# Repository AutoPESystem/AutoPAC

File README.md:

# AutoPAC
This repository will contain the relevant firmware and hardware for an automated PAC (Pump Assisted Clamping) Device.

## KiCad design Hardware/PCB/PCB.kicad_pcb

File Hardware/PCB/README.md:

# PCB
This is a KiCAD PCB project that contains the hardware implementation required for the AutoPAC device.

This includes a vacuum sensor, positive pressure sensor, circuitry to drive 2 brushed motors, circuitry to control multiple solenoid relays, and an LCD interface over SPI.

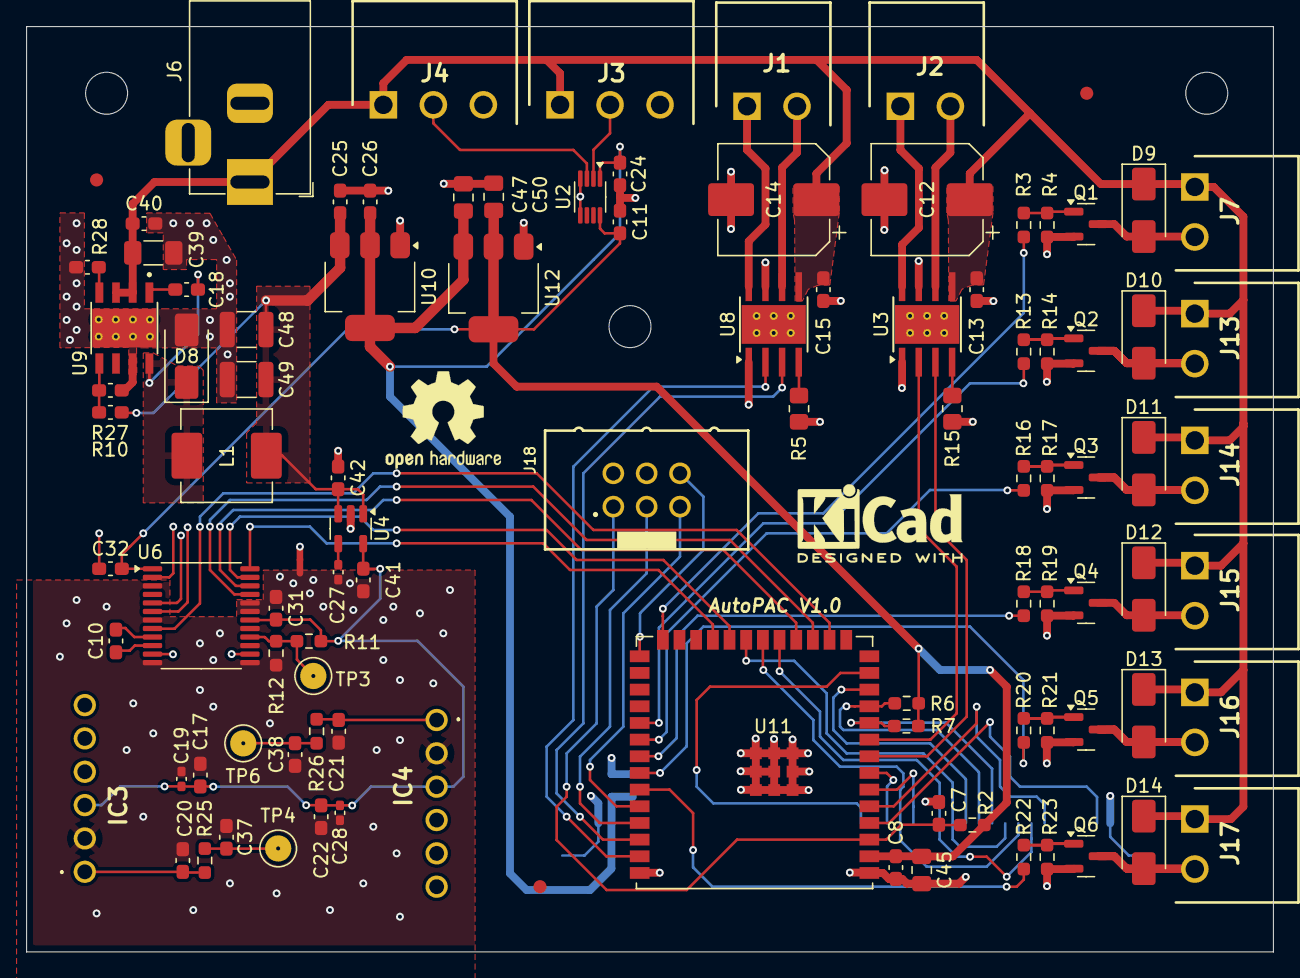
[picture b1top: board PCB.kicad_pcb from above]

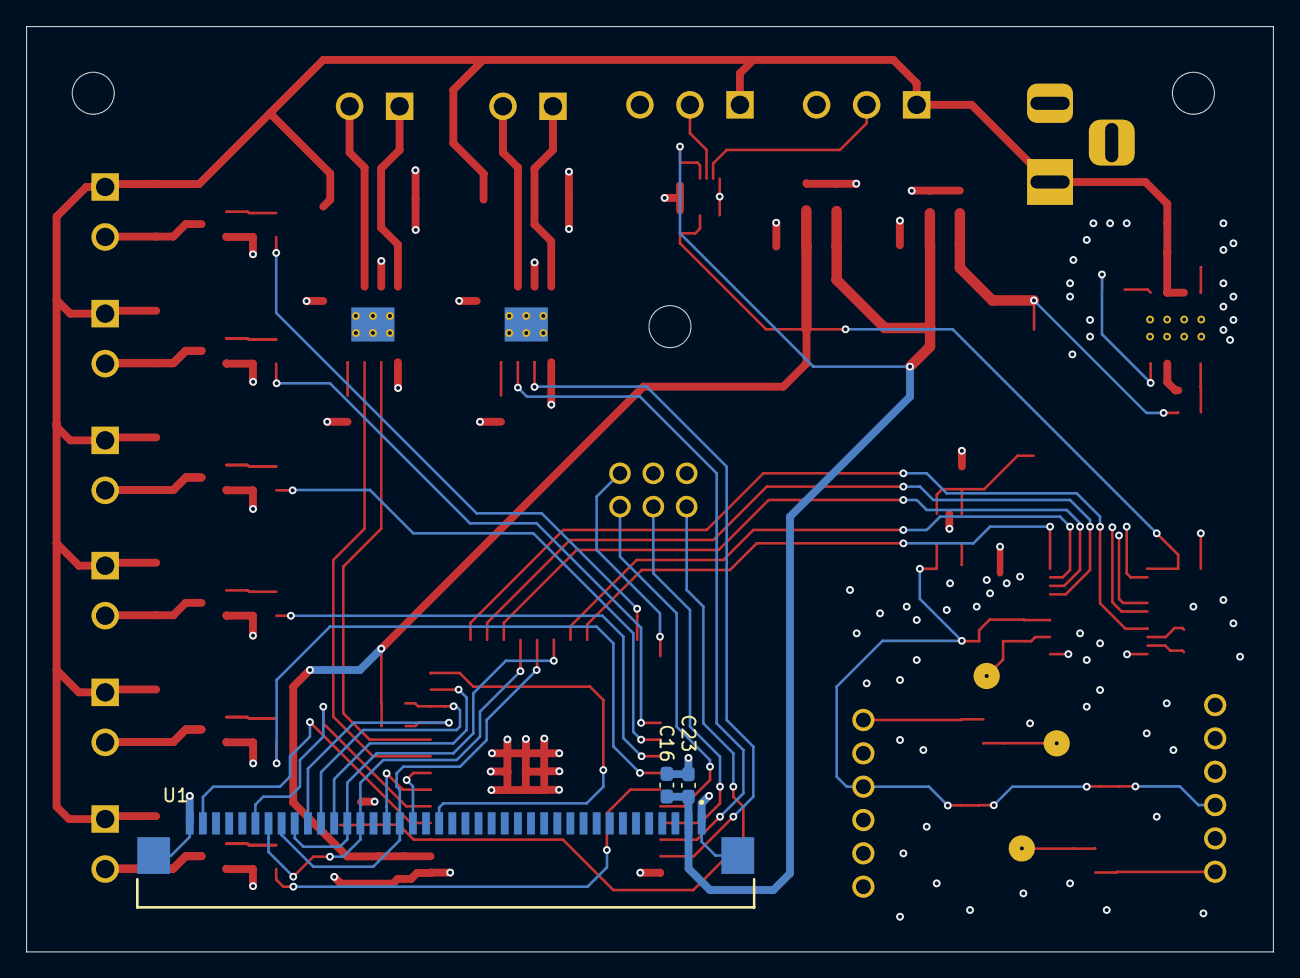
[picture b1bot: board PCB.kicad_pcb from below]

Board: 4 copper layers, 95.0 x 70.5 mm, 103 parts (3 on the bottom side), 69 nets.

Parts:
C7, C17, C22, C41, C42: 1uF; C_0603_1608Metric_Pad1.08x0.95mm_HandSolder
C8, C10, C11, C13, C15, C18, C23, C24, C31, C32, C40: 100nF; C_0603_1608Metric_Pad1.08x0.95mm_HandSolder
C12, C14: 22uF; CP_Elec_8x10
C16, C25, C26: 10uF; C_0603_1608Metric_Pad1.08x0.95mm_HandSolder
C19, C27, C28: 0.01uF; C_0402_1005Metric_Pad0.74x0.62mm_HandSolder
C20, C21: 470pF; C_0603_1608Metric_Pad1.08x0.95mm_HandSolder
C37, C38: 0.33uF; C_0603_1608Metric_Pad1.08x0.95mm_HandSolder
C39: 10uF; C_1206_3216Metric_Pad1.33x1.80mm_HandSolder
C45, C47, C50: 22uF; C_0805_2012Metric_Pad1.18x1.45mm_HandSolder
C48, C49: 47uF; C_1210_3225Metric
D8, D9, D10, D11, D12, D13, D14: SS310; D_SMA
H1, H2, H4: MountingHole; MountingHole_3.2mm_M3
IC3, IC4: MPX5500DP
J1, J2: Pump Motor; CONN_WJ15EDGRC-3.81-2P
J3, J4: BLDC Motor; CONN_WJ15EDGRC-3.81-3P
J6: XUNPU DC-005-A250; BarrelJack_Horizontal
J7, J13, J14, J15, J16, J17: Solenoid Terminal; CONN_WJ15EDGRC-3.81-2P
J18: Programmer; 61200621621
L1: 6.8uH; L_Changjiang_FXL0630
NT1: NetTie_2; NetTie-2_SMD_Pad0.5mm
Q1, Q2, Q3, Q4, Q5, Q6: MMBT2222A; SOT-23
R2, R4, R14, R17, R19, R21, R23: 10k; R_0603_1608Metric_Pad0.98x0.95mm_HandSolder
R3, R13, R16, R18, R20, R22: 470; R_0603_1608Metric_Pad0.98x0.95mm_HandSolder
R5, R15: 18k; R_0805_2012Metric_Pad1.20x1.40mm_HandSolder
R6, R7: 2.2k; R_0603_1608Metric_Pad0.98x0.95mm_HandSolder
R10: 66.5k; C_0603_1608Metric_Pad1.08x0.95mm_HandSolder
R11: 300; R_0603_1608Metric_Pad0.98x0.95mm_HandSolder
R12: 4.7k; R_0603_1608Metric_Pad0.98x0.95mm_HandSolder
R25, R26: 750; R_0603_1608Metric_Pad0.98x0.95mm_HandSolder
R27: 10.5k; C_0603_1608Metric_Pad1.08x0.95mm_HandSolder
R28: 45.3k; C_0603_1608Metric_Pad1.08x0.95mm_HandSolder
TP3, TP4, TP6: TestPoint_Probe; TestPoint_Keystone_5000-5004_Miniature
U1: ER-TFTM032-3; GCT_FFC3B07-40-T
U2: SN74LVC2T45DCUR; VSSOP-8_2.3x2mm_P0.5mm
U3, U8: DRV8871DDA; Texas_HTSOP-8-1EP_3.9x4.9mm_P1.27mm_EP2.95x4.9mm_Mask2.4x3.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
U4: SPX5205M5-L-5-0/TR; SOT-23-5
U6: ADS1232IPW; TSSOP-24_6.1x7.8mm_P0.65mm
U9: LMR16030PDDAR; VREG_LM5017MR_NOPB
U10: AZ1117-5.0; SOT-223-3_TabPin2
U11: ESP32-S3-WROOM-1U-N16R8; XCVR_ESP32-S3-WROOM-1U-N16R8
U12: AZ1117-3.3; SOT-223-3_TabPin2

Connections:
+3.3V: C8.2, C11.1, C32.1, C45.2, C50.1, R2.1, R6.1, R7.1, U2.8 (VCCB), U6.1 (DVDD), U11.2 (3V3), U12.2 (VO)
+4.7V: R11.2, R12.1, TP3.1, U6.16 (REFP)
+5.5V: C25.1, C42.2, C48.1, C49.1, L1.2, R10.1, U4.1 (IN), U4.3 (EN), U10.3 (VI)
+5V: C16.2, C23.2, C24.1, C26.1, C47.1, U1.2 (VDD), U2.1 (VCCA), U10.2 (VO), U12.3 (VI)
+5VA: C17.1, C19.1, C22.1, C28.1, C31.1, C41.2, IC3.3 (VCC), IC4.3 (VCC), R11.1, U4.5 (OUT), U6.18 (AVDD)
+24V: C12.1, C13.1, C14.1, C15.1, C39.1, C40.2, D9.1 (K), D10.1 (K), D11.1 (K), D12.1 (K), D13.1 (K), D14.1 (K), J3.1, J4.1, J6.1, J7.1, J13.1, J14.1, J15.1, J16.1, J17.1, U3.5 (VM), U8.5 (VM), U9.2 (VIN), U9.3 (EN)
/CTP-INT: U1.39 (CTP_INT), U11.4 (IO4)
/DISP-BACKLIGHT: U1.29 (BL_ON/OFF), U11.12 (IO8)
/DISP-CS: U1.23 (LCD_CS), U11.7 (IO7)
/DISP-DC: U1.25 (/WR(D/C)), U11.6 (IO6)
/DISP-RESET: U1.21 (RESET), U11.13 (IO19)
/ESP32-S3/BOOT: J18.6, U11.27 (IO0)
/ESP32-S3/EN: C7.2, J18.1, R2.2, U11.3 (EN)
/ESP32-S3/RX: J18.5, U11.36 (RXD0)
/ESP32-S3/TX: J18.3, U11.37 (TXD0)
/GPIO9: U6.21 (SPEED), U11.17 (IO9)
/GPIO10: U6.22 (~PWDN), U11.18 (IO10)
/GPIO14: U6.23 (SCLK), U11.22 (IO14)
/GPIO21: U6.24 (~DRDY/DOUT), U11.23 (IO21)
/GPIO46: U6.8 (A0), U11.16 (IO46)
/I2C-SCL: R6.2, U1.30 (CTP_SCL), U11.11 (IO18)
/I2C-SDA: R7.2, U1.31 (CTP_SDA), U11.10 (IO17)
/PUMP-IN1: U3.3 (IN1), U11.8 (IO15)
/PUMP-IN2: U3.2 (IN2), U11.9 (IO16)
/SOLENOID_1: R3.1, U11.26 (IO45)
/SOLENOID_2: R13.1, U11.31 (IO38)
/SOLENOID_3: R16.1, U11.32 (IO39)
/SOLENOID_4: R18.1, U11.33 (IO40)
/SOLENOID_5: R20.1, U11.34 (IO41)
/SOLENOID_6: R22.1, U11.35 (IO42)
/SPI-CLK: U1.24 (D/C(SCL)), U1.33 (SCLK), U11.20 (IO12)
/SPI-MISO: U1.28 (LCD_SDO), U1.32 (SDO), U11.21 (IO13)
/SPI-MOSI: U1.27 (LCD_SDI), U1.34 (SDI), U11.19 (IO11)
/VAC-IN1: U8.3 (IN1), U11.38 (IO2)
/VAC-IN2: U8.2 (IN2), U11.39 (IO1)
/buck/FB: R10.2, R27.1, U9.5 (FB)
/sensors/pressure_sensor1/SENSOR_VOUT: C38.2, R26.2, TP6.1, U6.14 (AINP2)
/sensors/pressure_sensor/SENSOR_VOUT: C37.2, R25.2, TP4.1, U6.11 (AINP1)
/uSD-CS: U1.35 (SD_/CS), U11.5 (IO5)
GND: C7.1, C8.1, C11.2, C12.2, C13.2, C14.2, C15.2, C16.1, C23.1, C24.2, C25.2, C26.2, C32.2, C39.2, C40.1, C42.1, C45.1, C47.2, C48.2, C49.2, C50.2, D8.2 (A), J3.3, J4.3, J6.2, J18.4, NT1.2, Q1.2 (E), Q2.2 (E), Q3.2 (E), Q4.2 (E), Q5.2 (E), Q6.2 (E), R4.2, R5.2, R14.2, R15.2, R17.2, R19.2, R21.2, R23.2, R27.2, R28.2, U1.1 (GND), U1.40 (GND), U1.S1, U1.S2, U2.4 (GND), U2.5 (DIR), U3.1 (GND), U3.7 (GND), U3.9 (GND), U4.2 (GND), U6.2 (DGND), U6.5 (DGND), U6.6 (DGND), U8.1 (GND), U8.7 (GND), U8.9 (GND), U9.7 (GND), U9.9 (THERMALPAD), U9.10, U9.11, U9.12, U9.13, U9.14, U9.15, U9.16, U9.17, U10.1 (GND), U11.1 (GND), U11.40 (GND__1), U11.41_1 (GND__2), U11.41_2 (GND__3), U11.41_3 (GND__4), U11.41_4 (GND__5), U11.41_5 (GND__6), U11.41_6 (GND__7), U11.41_7 (GND__8), U11.41_8 (GND__9), U11.41_9 (GND__10), U12.1 (GND)
GNDA: C17.2, C19.2, C20.1, C21.1, C22.2, C27.1, C28.2, C31.2, C37.1, C38.1, C41.1, IC3.2 (GROUND), IC4.2 (GROUND), NT1.1, R12.2, U6.3 (CLKIN/XTAL1), U6.7 (TEMP), U6.12 (AINN1), U6.13 (AINN2), U6.15 (REFN), U6.17 (AGND), U6.19 (GAIN0), U6.20 (GAIN1)
unnamed: C10.1, U6.9 (CAP)
unnamed: C10.2, U6.10 (CAP)
unnamed: C18.2, D8.1 (K), L1.1, U9.8 (SW)
unnamed: D9.2 (A), J7.2, Q1.3 (C)
unnamed: D10.2 (A), J13.2, Q2.3 (C)
unnamed: D11.2 (A), J14.2, Q3.3 (C)
unnamed: D12.2 (A), J15.2, Q4.3 (C)
unnamed: D13.2 (A), J16.2, Q5.3 (C)
unnamed: D14.2 (A), J17.2, Q6.3 (C)
unnamed: C20.2, IC3.1 (VOUT), R25.1
unnamed: C21.2, IC4.1 (VOUT), R26.1
unnamed: J1.1, U8.8 (OUT2)
unnamed: J1.2, U8.6 (OUT1)
unnamed: J2.1, U3.8 (OUT2)
unnamed: J2.2, U3.6 (OUT1)
unnamed: J3.2, U2.2 (A1)
unnamed: J4.2, U2.3 (A2)
unnamed: Q1.1 (B), R3.2, R4.1
unnamed: Q2.1 (B), R13.2, R14.1
unnamed: Q3.1 (B), R16.2, R17.1
unnamed: Q4.1 (B), R18.2, R19.1
unnamed: Q5.1 (B), R20.2, R21.1
unnamed: Q6.1 (B), R22.2, R23.1
unnamed: R15.1, U3.4 (ILIM)
unnamed: C27.2, U4.4 (BP)
unnamed: R5.1, U8.4 (ILIM)
unnamed: C18.1, U9.1 (BOOT)
unnamed: R28.1, U9.4 (RT/SYNC)

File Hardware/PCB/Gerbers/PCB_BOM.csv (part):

Comment,Designator,Footprint,LCSC Part Number
50V 1uF X5R ±10% 0603 Multilayer Ceramic Capacitors MLCC - SMD/SMT ROHS,C7,Capacitor_SMD:C_0603_1608Metric_Pad1.08x0.95mm_HandSolder,C15849
50V 100nF X7R ±10% 0603 Multilayer Ceramic Capacitors MLCC - SMD/SMT ROHS,C8,Capacitor_SMD:C_0603_1608Metric_Pad1.08x0.95mm_HandSolder,C14663
50V 100nF X7R ±10% 0603 Multilayer Ceramic Capacitors MLCC - SMD/SMT ROHS,C10,Capacitor_SMD:C_0603_1608Metric_Pad1.08x0.95mm_HandSolder,C14663
50V 100nF X7R ±10% 0603 Multilayer Ceramic Capacitors MLCC - SMD/SMT ROHS,C11,Capacitor_SMD:C_0603_1608Metric_Pad1.08x0.95mm_HandSolder,C14663
"22uF 100V ±20% SMD,D8xL10.5mm Aluminum Electrolytic Capacitors - SMD ROHS",C12,Capacitor_SMD:CP_Elec_8x10,C29144
50V 100nF X7R ±10% 0603 Multilayer Ceramic Capacitors MLCC - SMD/SMT ROHS,C13,Capacitor_SMD:C_0603_1608Metric_Pad1.08x0.95mm_HandSolder,C14663
"22uF 100V ±20% SMD,D8xL10.5mm Aluminum Electrolytic Capacitors - SMD ROHS",C14,Capacitor_SMD:CP_Elec_8x10,C29144
50V 100nF X7R ±10% 0603 Multilayer Ceramic Capacitors MLCC - SMD/SMT ROHS,C15,Capacitor_SMD:C_0603_1608Metric_Pad1.08x0.95mm_HandSolder,C14663
25V 10uF X5R ±20% 0603 Multilayer Ceramic Capacitors MLCC - SMD/SMT ROHS,C16,Capacitor_SMD:C_0603_1608Metric_Pad1.08x0.95mm_HandSolder,C96446
50V 1uF X5R ±10% 0603 Multilayer Ceramic Capacitors MLCC - SMD/SMT ROHS,C17,Capacitor_SMD:C_0603_1608Metric_Pad1.08x0.95mm_HandSolder,C15849
50V 100nF X7R ±10% 0603 Multilayer Ceramic Capacitors MLCC - SMD/SMT ROHS,C18,Capacitor_SMD:C_0603_1608Metric_Pad1.08x0.95mm_HandSolder,C14663
10000 pF ±10% 50V Ceramic Capacitor X7R 0402 (1005 Metric),C19,Capacitor_SMD:C_0402_1005Metric_Pad0.74x0.62mm_HandSolder,C15195
50V 470pF NP0 ±5% 0603 Multilayer Ceramic Capacitors MLCC - SMD/SMT ROHS,C20,Capacitor_SMD:C_0603_1608Metric_Pad1.08x0.95mm_HandSolder,C106211
50V 470pF NP0 ±5% 0603 Multilayer Ceramic Capacitors MLCC - SMD/SMT ROHS,C21,Capacitor_SMD:C_0603_1608Metric_Pad1.08x0.95mm_HandSolder,C106211
50V 1uF X5R ±10% 0603 Multilayer Ceramic Capacitors MLCC - SMD/SMT ROHS,C22,Capacitor_SMD:C_0603_1608Metric_Pad1.08x0.95mm_HandSolder,C15849
50V 100nF X7R ±10% 0603 Multilayer Ceramic Capacitors MLCC - SMD/SMT ROHS,C23,Capacitor_SMD:C_0603_1608Metric_Pad1.08x0.95mm_HandSolder,C14663
50V 100nF X7R ±10% 0603 Multilayer Ceramic Capacitors MLCC - SMD/SMT ROHS,C24,Capacitor_SMD:C_0603_1608Metric_Pad1.08x0.95mm_HandSolder,C14663
25V 10uF X5R ±20% 0603 Multilayer Ceramic Capacitors MLCC - SMD/SMT ROHS,C25,Capacitor_SMD:C_0603_1608Metric_Pad1.08x0.95mm_HandSolder,C96446
25V 10uF X5R ±20% 0603 Multilayer Ceramic Capacitors MLCC - SMD/SMT ROHS,C26,Capacitor_SMD:C_0603_1608Metric_Pad1.08x0.95mm_HandSolder,C96446
10000 pF ±10% 50V Ceramic Capacitor X7R 0402 (1005 Metric),C27,Capacitor_SMD:C_0402_1005Metric_Pad0.74x0.62mm_HandSolder,C15195
10000 pF ±10% 50V Ceramic Capacitor X7R 0402 (1005 Metric),C28,Capacitor_SMD:C_0402_1005Metric_Pad0.74x0.62mm_HandSolder,C15195
50V 100nF X7R ±10% 0603 Multilayer Ceramic Capacitors MLCC - SMD/SMT ROHS,C31,Capacitor_SMD:C_0603_1608Metric_Pad1.08x0.95mm_HandSolder,C14663
50V 100nF X7R ±10% 0603 Multilayer Ceramic Capacitors MLCC - SMD/SMT ROHS,C32,Capacitor_SMD:C_0603_1608Metric_Pad1.08x0.95mm_HandSolder,C14663
25V 0.33uF X7R ±10% 0603 Multilayer Ceramic Capacitors MLCC - SMD/SMT ROHS,C37,Capacitor_SMD:C_0603_1608Metric_Pad1.08x0.95mm_HandSolder,C5139492
25V 0.33uF X7R ±10% 0603 Multilayer Ceramic Capacitors MLCC - SMD/SMT ROHS,C38,Capacitor_SMD:C_0603_1608Metric_Pad1.08x0.95mm_HandSolder,C5139492
50V 10uF X5R ±10% 1206 Multilayer Ceramic Capacitors MLCC - SMD/SMT ROHS,C39,Capacitor_SMD:C_1206_3216Metric_Pad1.33x1.80mm_HandSolder,C13585
50V 100nF X7R ±10% 0603 Multilayer Ceramic Capacitors MLCC - SMD/SMT ROHS,C40,Capacitor_SMD:C_0603_1608Metric_Pad1.08x0.95mm_HandSolder,C14663
50V 1uF X5R ±10% 0603 Multilayer Ceramic Capacitors MLCC - SMD/SMT ROHS,C41,Capacitor_SMD:C_0603_1608Metric_Pad1.08x0.95mm_HandSolder,C15849
50V 1uF X5R ±10% 0603 Multilayer Ceramic Capacitors MLCC - SMD/SMT ROHS,C42,Capacitor_SMD:C_0603_1608Metric_Pad1.08x0.95mm_HandSolder,C15849
25V 22uF X5R ±20% 0805 Multilayer Ceramic Capacitors MLCC - SMD/SMT ROHS,C45,Capacitor_SMD:C_0805_2012Metric_Pad1.18x1.45mm_HandSolder,C602037
25V 22uF X5R ±20% 0805 Multilayer Ceramic Capacitors MLCC - SMD/SMT ROHS,C47,Capacitor_SMD:C_0805_2012Metric_Pad1.18x1.45mm_HandSolder,C602037
16V 47uF X5R ±10% 1210 Multilayer Ceramic Capacitors MLCC - SMD/SMT ROHS,C48,Capacitor_SMD:C_1210_3225Metric,C77101
16V 47uF X5R ±10% 1210 Multilayer Ceramic Capacitors MLCC - SMD/SMT ROHS,C49,Capacitor_SMD:C_1210_3225Metric,C77101
25V 22uF X5R ±20% 0805 Multilayer Ceramic Capacitors MLCC - SMD/SMT ROHS,C50,Capacitor_SMD:C_0805_2012Metric_Pad1.18x1.45mm_HandSolder,C602037
100V Independent Type 850mV@3A 3A SMA(DO-214AC) Schottky Diodes ROHS,D8,Diode_SMD:D_SMA,C15874
100V Independent Type 850mV@3A 3A SMA(DO-214AC) Schottky Diodes ROHS,D9,Diode_SMD:D_SMA,C15874
100V Independent Type 850mV@3A 3A SMA(DO-214AC) Schottky Diodes ROHS,D10,Diode_SMD:D_SMA,C15874
100V Independent Type 850mV@3A 3A SMA(DO-214AC) Schottky Diodes ROHS,D11,Diode_SMD:D_SMA,C15874
100V Independent Type 850mV@3A 3A SMA(DO-214AC) Schottky Diodes ROHS,D12,Diode_SMD:D_SMA,C15874
100V Independent Type 850mV@3A 3A SMA(DO-214AC) Schottky Diodes ROHS,D13,Diode_SMD:D_SMA,C15874
100V Independent Type 850mV@3A 3A SMA(DO-214AC) Schottky Diodes ROHS,D14,Diode_SMD:D_SMA,C15874
"Bend -40℃~+105℃ 1 3.81mm 300V 8A 2 1x2P Receptacle-Close Push-Pull,P=3.81mm Pluggable System Terminal Block ROHS",J1,Vendor_Footprints:CONN_WJ15EDGRC-3.81-2P,C8387
"Bend -40℃~+105℃ 1 3.81mm 300V 8A 2 1x2P Receptacle-Close Push-Pull,P=3.81mm Pluggable System Terminal Block ROHS",J2,Vendor_Footprints:CONN_WJ15EDGRC-3.81-2P,C8387
"Bend -40℃~+105℃ 1 3.81mm 300V 8A 3 1x3P Receptacle-Close Push-Pull,P=3.81mm Pluggable System Terminal Block ROHS",J3,Vendor_Footprints:CONN_WJ15EDGRC-3.81-3P,C8406
"Bend -40℃~+105℃ 1 3.81mm 300V 8A 3 1x3P Receptacle-Close Push-Pull,P=3.81mm Pluggable System Terminal Block ROHS",J4,Vendor_Footprints:CONN_WJ15EDGRC-3.81-3P,C8406
Bend-in DC Power Receptacle -20℃~+70℃ 2.5mm 6.3mm 5A 30V Plugin DC Power Connectors ROHS,J6,Connector_BarrelJack:BarrelJack_Horizontal,C720558
"Bend -40℃~+105℃ 1 3.81mm 300V 8A 2 1x2P Receptacle-Close Push-Pull,P=3.81mm Pluggable System Terminal Block ROHS",J7,Vendor_Footprints:CONN_WJ15EDGRC-3.81-2P,C8387
"Bend -40℃~+105℃ 1 3.81mm 300V 8A 2 1x2P Receptacle-Close Push-Pull,P=3.81mm Pluggable System Terminal Block ROHS",J13,Vendor_Footprints:CONN_WJ15EDGRC-3.81-2P,C8387
"Bend -40℃~+105℃ 1 3.81mm 300V 8A 2 1x2P Receptacle-Close Push-Pull,P=3.81mm Pluggable System Terminal Block ROHS",J14,Vendor_Footprints:CONN_WJ15EDGRC-3.81-2P,C8387
"Bend -40℃~+105℃ 1 3.81mm 300V 8A 2 1x2P Receptacle-Close Push-Pull,P=3.81mm Pluggable System Terminal Block ROHS",J15,Vendor_Footprints:CONN_WJ15EDGRC-3.81-2P,C8387
"Bend -40℃~+105℃ 1 3.81mm 300V 8A 2 1x2P Receptacle-Close Push-Pull,P=3.81mm Pluggable System Terminal Block ROHS",J16,Vendor_Footprints:CONN_WJ15EDGRC-3.81-2P,C8387
"Bend -40℃~+105℃ 1 3.81mm 300V 8A 2 1x2P Receptacle-Close Push-Pull,P=3.81mm Pluggable System Terminal Block ROHS",J17,Vendor_Footprints:CONN_WJ15EDGRC-3.81-2P,C8387
"2.54mm -40℃~+105℃ Direct Insert 3A 2x3P 250V 3 Simple cow constellation 2.54mm 2 Plugin,P=2.54mm IDC Connectors ROHS",J18,Vendor_Footprints:61200621621,C492441
"5A 6.8uH Winding Inductor ±20% 6A SMD,6.6x7mm Power Inductors ROHS",L1,Inductor_SMD:L_Changjiang_FXL0630,C167221
"600mA Ic, 40V Vce, NPN Transistor, SOT-23",Q1,Package_TO_SOT_SMD:SOT-23,C916372
"600mA Ic, 40V Vce, NPN Transistor, SOT-23",Q2,Package_TO_SOT_SMD:SOT-23,C916372
"600mA Ic, 40V Vce, NPN Transistor, SOT-23",Q3,Package_TO_SOT_SMD:SOT-23,C916372
"600mA Ic, 40V Vce, NPN Transistor, SOT-23",Q4,Package_TO_SOT_SMD:SOT-23,C916372
"600mA Ic, 40V Vce, NPN Transistor, SOT-23",Q5,Package_TO_SOT_SMD:SOT-23,C916372
"600mA Ic, 40V Vce, NPN Transistor, SOT-23",Q6,Package_TO_SOT_SMD:SOT-23,C916372
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
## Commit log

2025-02-21 added README to PCB
2025-02-21 added a lot of stuff, going to work on LCD + Touch next
2025-02-21 added symbol for LCD, working on adding PWM output terminal for brushless pump motors
2025-02-21 Added brushless DC support, fixed terminal blocks too
2025-02-24 switched to making buck converter to save costs and space, and to allow for LDO after 5.5V for better stability
2025-02-24 swapped to be better precision resistors for feedback on buck and votlage reference for ADCs
2025-02-24 consolidated IO for LCD block, broke out hierarchial pins, need to start wiring everything up and then on to layout
2025-03-02 overall design is pretty much done, starting layout and routing now
2025-03-04 pcb layout and routing pretty much done, checking DRC
2025-03-04 fixed BOM, added some silkscreen, getting quote now
2025-03-04 kinda pricey, I should try to make a smaller version using LCSC parts for cheaper solution
2025-03-05 done with this, placed order
2025-03-05 fixed various hole sizes, fixed unconnected signals to ADC, pcbs have been ordered
